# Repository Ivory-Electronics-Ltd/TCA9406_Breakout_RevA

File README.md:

# TCA9406 Breakout Board — Rev A

**Ivory Electronics** | KiCAD 9.0 | 2-Layer PCB

A compact breakout board for the Texas Instruments **TCA9406DCUR**, a 2-bit bidirectional I2C/SMBus voltage-level translator with 8-kV HBM ESD protection. Designed to bridge two I2C buses operating at different voltage levels (e.g., 1.8V ↔ 3.3V, 3.3V ↔ 5V) with onboard optional pull-up resistors for rapid prototyping.

---

## Key Specifications

| Parameter | Value |
|---|---|
| Main IC | TCA9406DCUR (VSSOP-8, 2.3×2 mm, 0.5 mm pitch) |
| I2C Channels | 2 (SCL + SDA) |
| Max I2C Speed | 1 MHz |
| VCCA Range | 0.9 V – 3.6 V |
| VCCB Range | 0.9 V – 5.5 V |
| ESD Protection | 8 kV HBM |
| Direction Control | Automatic (no DIR pin) |
| PCB Size | 30 mm × 19 mm |
| PCB Layers | 2 (FR4, 1.6 mm) |
| Corner Radius | 3 mm |
| LCSC Part No. | C840107 |

---

## Schematic Overview

The board routes Side A and Side B I2C signals through U1 with independent power supplies on each side. The EN pin is permanently pulled high via R5, keeping the translator always enabled.

```
  [J1 — Connector A]           [J2 — Connector B]
  Pin 1: VCCA                  Pin 1: VCCB
  Pin 2: GND                   Pin 2: GND
  Pin 3: SCL_A                 Pin 3: SCL_B
  Pin 4: SDA_A                 Pin 4: SDA_B
         |                            |
         +----[U1: TCA9406DCUR]-------+
                  EN ← R5 (10k) ← VCCA
```

### Connectors

| Ref | Type | Pinout |
|---|---|---|
| J1 | 1×4 2.54 mm pin header | VCCA, GND, SCL_A, SDA_A |
| J2 | 1×4 2.54 mm pin header | VCCB, GND, SCL_B, SDA_B |

### Optional Pull-Up Resistors

Four solder jumpers select whether the onboard 10 kΩ pull-ups are connected. All are **open (disabled) by default**.

| Jumper | Signal | Resistor |
|---|---|---|
| JP1 | SDA_A | R1 (10 kΩ) to VCCA |
| JP2 | SCL_A | R2 (10 kΩ) to VCCA |
| JP3 | SDA_B | R3 (10 kΩ) to VCCB |
| JP4 | SCL_B | R4 (10 kΩ) to VCCB |

Close a jumper by bridging the two pads with solder. Leave open if your host system or target device already provides pull-ups.

### Decoupling

| Ref | Value | Location |
|---|---|---|
| C1, C3 | 1 µF 0603 | VCCA / VCCB bulk decoupling |
| C2, C4 | 100 nF 0603 | VCCA / VCCB HF decoupling |

### Test Points

| Ref | Signal |
|---|---|
| TP1 | GND |
| TP2 | VCCA |
| TP3 | VCCB |
| TP4 | SDA_A |
| TP5 | SDA_B |
| TP6 | SCL_A |
| TP7 | SCL_B |

All test points use 1.5 mm SMD pads.

---

## PCB Details

| Parameter | Value |
|---|---|
| Stackup | 2-layer FR4 |
| Board thickness | 1.6 mm |
| Copper thickness | 35 µm (1 oz) |
| Min clearance | 0.1016 mm |
| Min track width | 0.2 mm |
| Via (OD / drill) | 0.6 mm / 0.4 mm |
| Ground pour | Both layers |
| Teardrops | Enabled (PTH pads, vias, SMD pads) |
| Corner style | Rounded, r = 3 mm |

All resistors and capacitors use **0603 hand-solder footprints** with enlarged pads for ease of assembly.

---

## Bill of Materials (Abridged)

| Ref | Qty | Value / Part | Package | LCSC |
|---|---|---|---|---|
| U1 | 1 | TCA9406DCUR | VSSOP-8 | C840107 |
| R1–R5 | 5 | 10 kΩ | 0603 | — |
| C1, C3 | 2 | 1 µF | 0603 | — |
| C2, C4 | 2 | 100 nF | 0603 | — |
| J1, J2 | 2 | 1×4 2.54 mm pin header | Through-hole | — |
| JP1–JP4 | 4 | Solder jumper (2-pad, open) | 1.3 mm pitch | — |
| TP1–TP7 | 7 | Test point | SMD 1.5 mm pad | — |

---

## Usage Notes

- Supply **VCCA** and **VCCB** independently to match the voltage levels of the two I2C domains.
- The translator is **bidirectional and auto-sensing** — no firmware or direction control is needed.
- R5 (10 kΩ) pulls EN high from VCCA permanently. To disable the translator, cut the R5 pad or replace with a header and drive EN low externally.
- Close JP1–JP4 only if external pull-ups are absent on that signal line. Double pull-ups will lower the effective resistance and may violate I2C specifications for your bus capacitance.

---

## Repository

| File | Description |
|---|---|
| `TCA9406_Breakout_RevA.kicad_sch` | Schematic |
| `TCA9406_Breakout_RevA.kicad_pcb` | PCB layout |
| `TCA9406_Breakout_RevA.kicad_pro` | KiCAD project file |
| `TCA9406_Breakout_RevA-backups/` | KiCAD auto-backups |

Designed with **KiCAD 9.0**. Datasheet: [TCA9406 (ti.com)](https://www.ti.com/lit/ds/symlink/tca9406.pdf)

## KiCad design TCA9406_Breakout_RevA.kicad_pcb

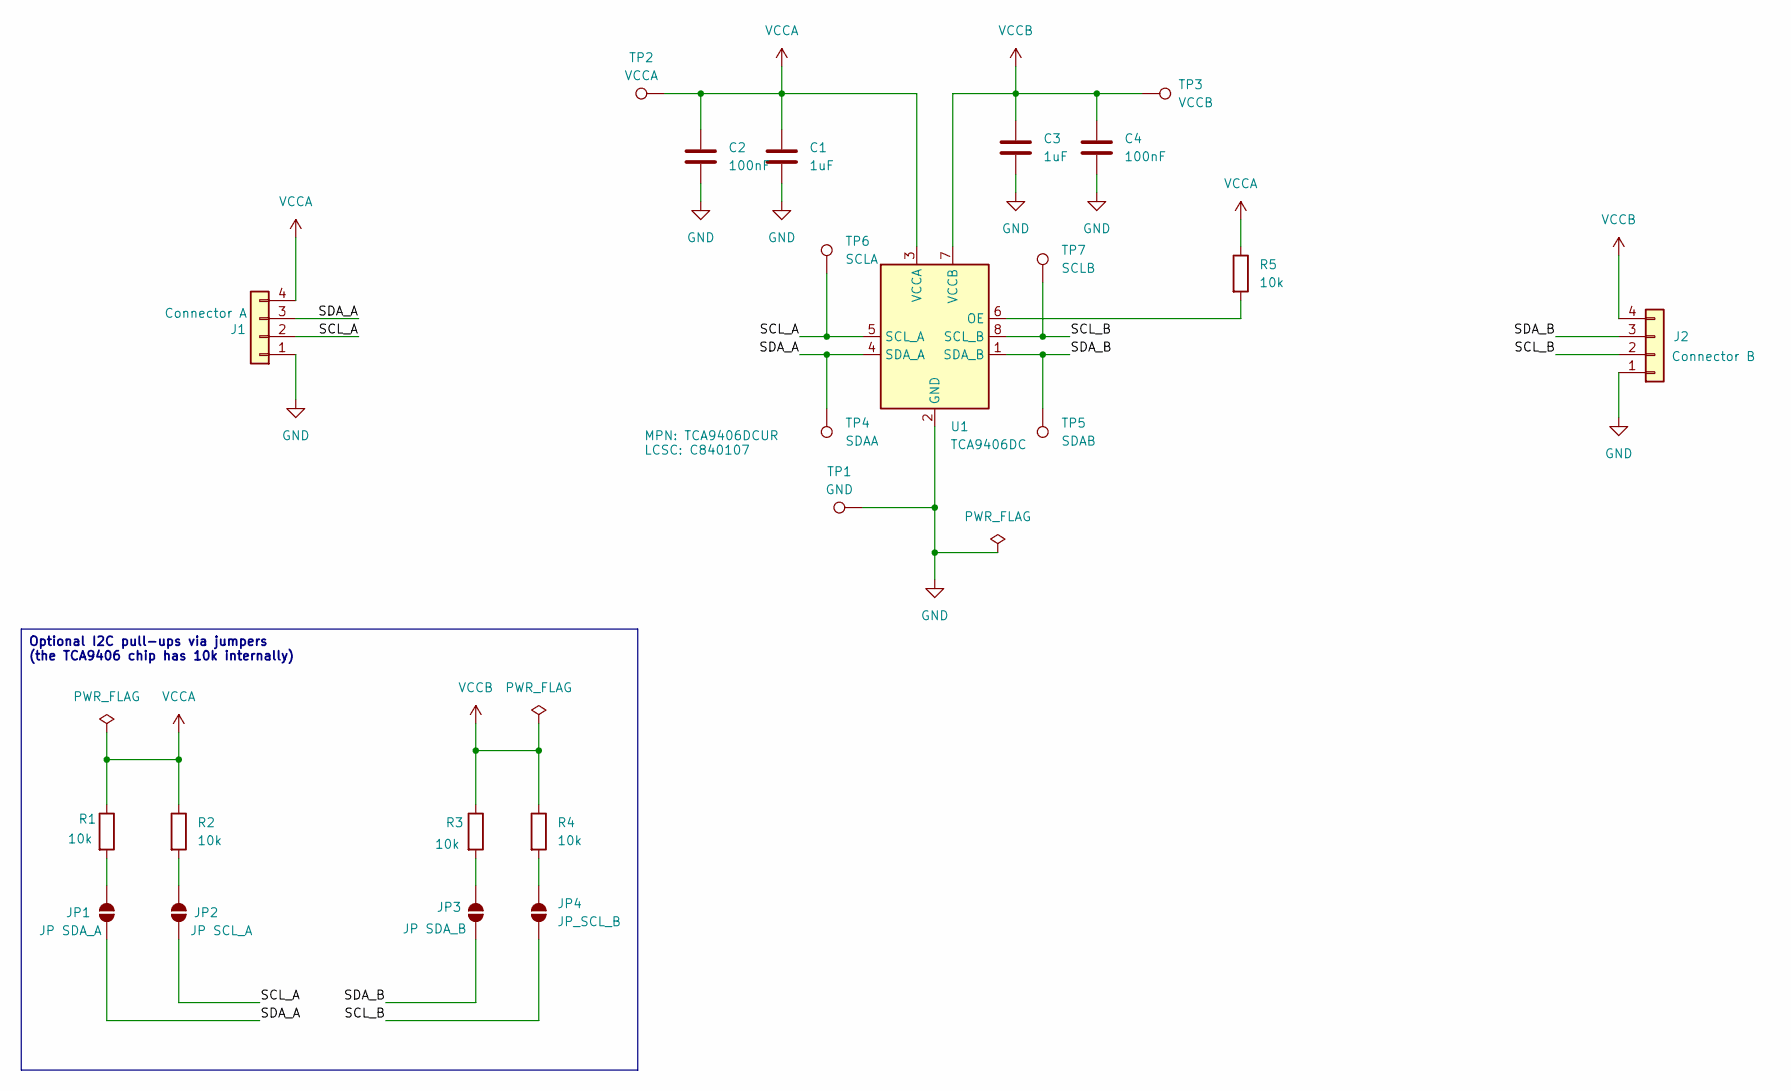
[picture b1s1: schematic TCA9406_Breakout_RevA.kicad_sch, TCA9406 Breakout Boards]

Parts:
C1, C3: 1uF; C_0603_1608Metric_Pad1.08x0.95mm_HandSolder
C2, C4: 100nF; C_0603_1608Metric_Pad1.08x0.95mm_HandSolder
J1: Connector A; PinHeader_1x04_P2.54mm_Vertical
J2: Connector B; PinHeader_1x04_P2.54mm_Vertical
JP1: JP SDA_A; SolderJumper-2_P1.3mm_Open_RoundedPad1.0x1.5mm
JP2: JP SCL_A; SolderJumper-2_P1.3mm_Open_RoundedPad1.0x1.5mm
JP3: JP SDA_B; SolderJumper-2_P1.3mm_Open_RoundedPad1.0x1.5mm
JP4: JP_SCL_B; SolderJumper-2_P1.3mm_Open_RoundedPad1.0x1.5mm
R1, R2, R3, R4, R5: 10k; R_0603_1608Metric_Pad0.98x0.95mm_HandSolder
TP1: GND; TestPoint_Pad_D1.5mm
TP2: VCCA; TestPoint_Pad_D1.5mm
TP3: VCCB; TestPoint_Pad_D1.5mm
TP4: SDAA; TestPoint_Pad_D1.5mm
TP5: SDAB; TestPoint_Pad_D1.5mm
TP6: SCLA; TestPoint_Pad_D1.5mm
TP7: SCLB; TestPoint_Pad_D1.5mm
U1: TCA9406DC; VSSOP-8_2.3x2mm_P0.5mm; MPN TCA9406DCUR; LCSC C840107

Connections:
/SCL_A: J1.2, JP2.1 (A), TP6.1, U1.5 (SCL_A)
/SCL_B: J2.2, JP4.1 (A), TP7.1, U1.8 (SCL_B)
/SDA_A: J1.3, JP1.1 (A), TP4.1, U1.4 (SDA_A)
/SDA_B: J2.3, JP3.1 (A), TP5.1, U1.1 (SDA_B)
GND: C1.2, C2.2, C3.2, C4.2, J1.1, J2.1, TP1.1, U1.2 (GND)
unnamed: JP1.2 (B), R1.2
unnamed: JP2.2 (B), R2.2
unnamed: JP3.2 (B), R3.2
unnamed: JP4.2 (B), R4.2
unnamed: R5.2, U1.6 (OE)
VCCA: C1.1, C2.1, J1.4, R1.1, R2.1, R5.1, TP2.1, U1.3 (VCCA)
VCCB: C3.1, C4.1, J2.4, R3.1, R4.1, TP3.1, U1.7 (VCCB)

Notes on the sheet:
Optional I2C pull-ups via jumpers (the TCA9406 chip has 10k internally)

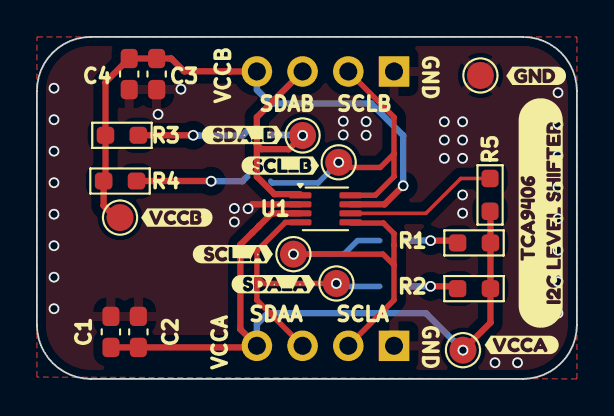
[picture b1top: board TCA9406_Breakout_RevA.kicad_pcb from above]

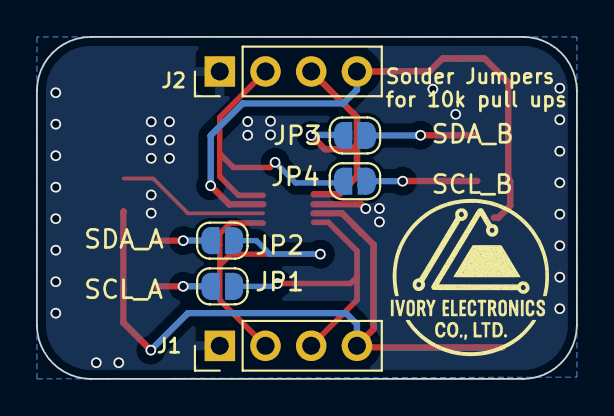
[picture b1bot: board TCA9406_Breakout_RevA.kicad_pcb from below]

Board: 2 copper layers, 30.0 x 19.0 mm, 31 parts (6 on the bottom side), 12 nets.

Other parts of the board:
kibuzzard-6A3A9CA2: G***; kibuzzard-6A3A9CA2
kibuzzard-6A3A9CA9: G***; kibuzzard-6A3A9CA9
kibuzzard-6A3A9CB1: G***; kibuzzard-6A3A9CB1
kibuzzard-6A3A9CB7: G***; kibuzzard-6A3A9CB7
kibuzzard-6A3A9CE7: G***; kibuzzard-6A3A9CE7
kibuzzard-6A3A9CEE: G***; kibuzzard-6A3A9CEE
kibuzzard-6A3A9D00: G***; kibuzzard-6A3A9D00
kibuzzard-6A3A9D08: G***; kibuzzard-6A3A9D08

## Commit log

2026-06-19 Initial commit of TCA9406 Breakout RevA project files
2026-06-19 minor layout change
2026-06-20 Fixing ground plane
2026-06-23 Add comprehensive README.md
